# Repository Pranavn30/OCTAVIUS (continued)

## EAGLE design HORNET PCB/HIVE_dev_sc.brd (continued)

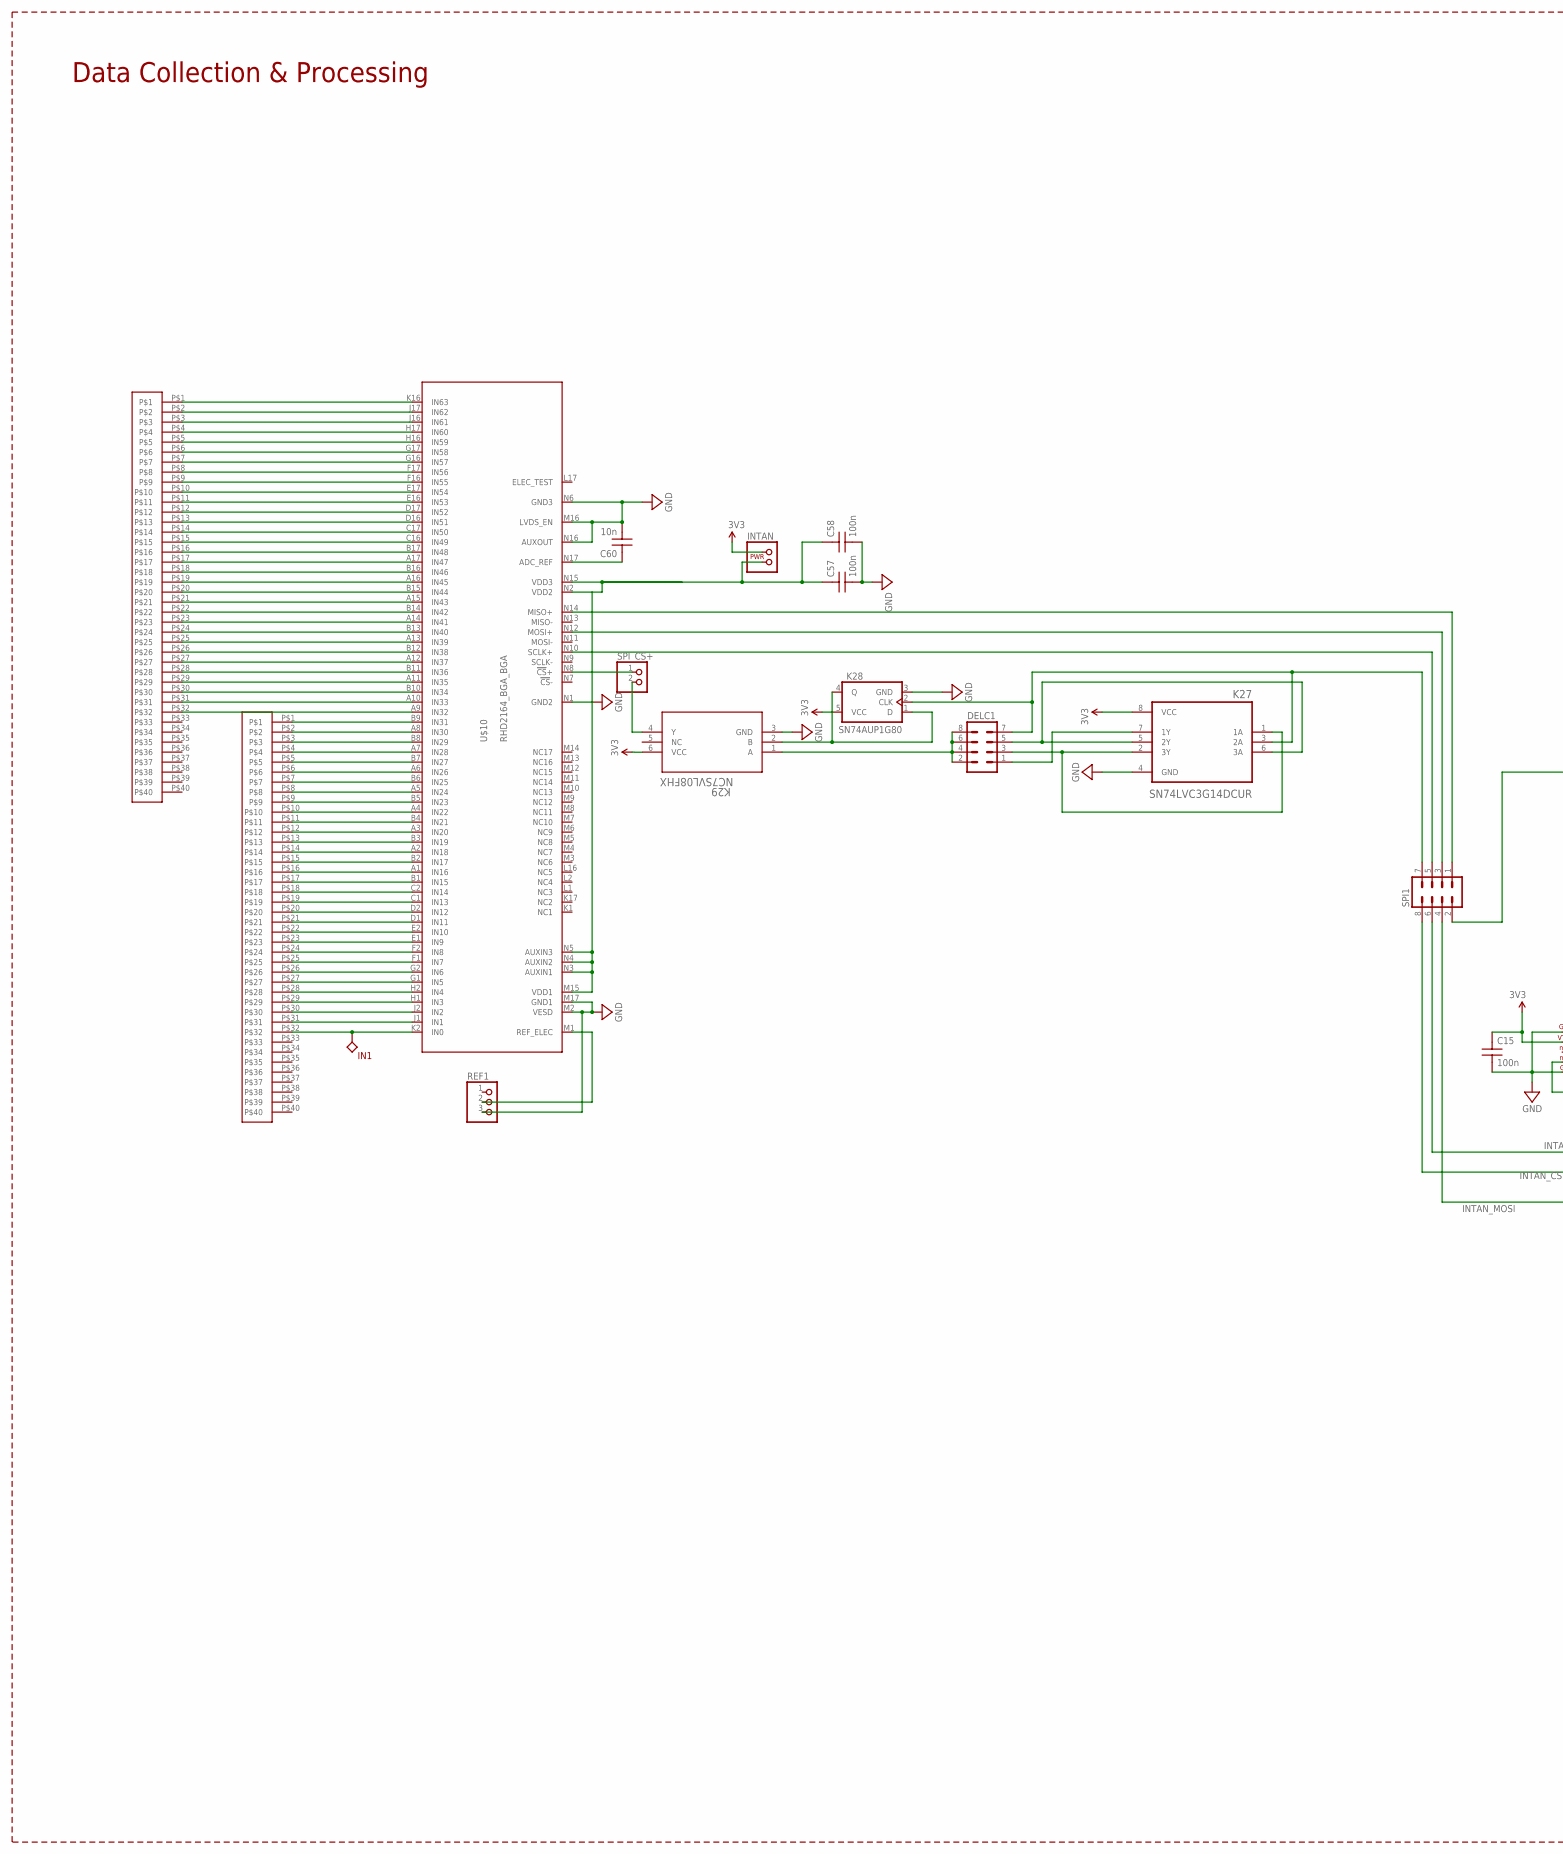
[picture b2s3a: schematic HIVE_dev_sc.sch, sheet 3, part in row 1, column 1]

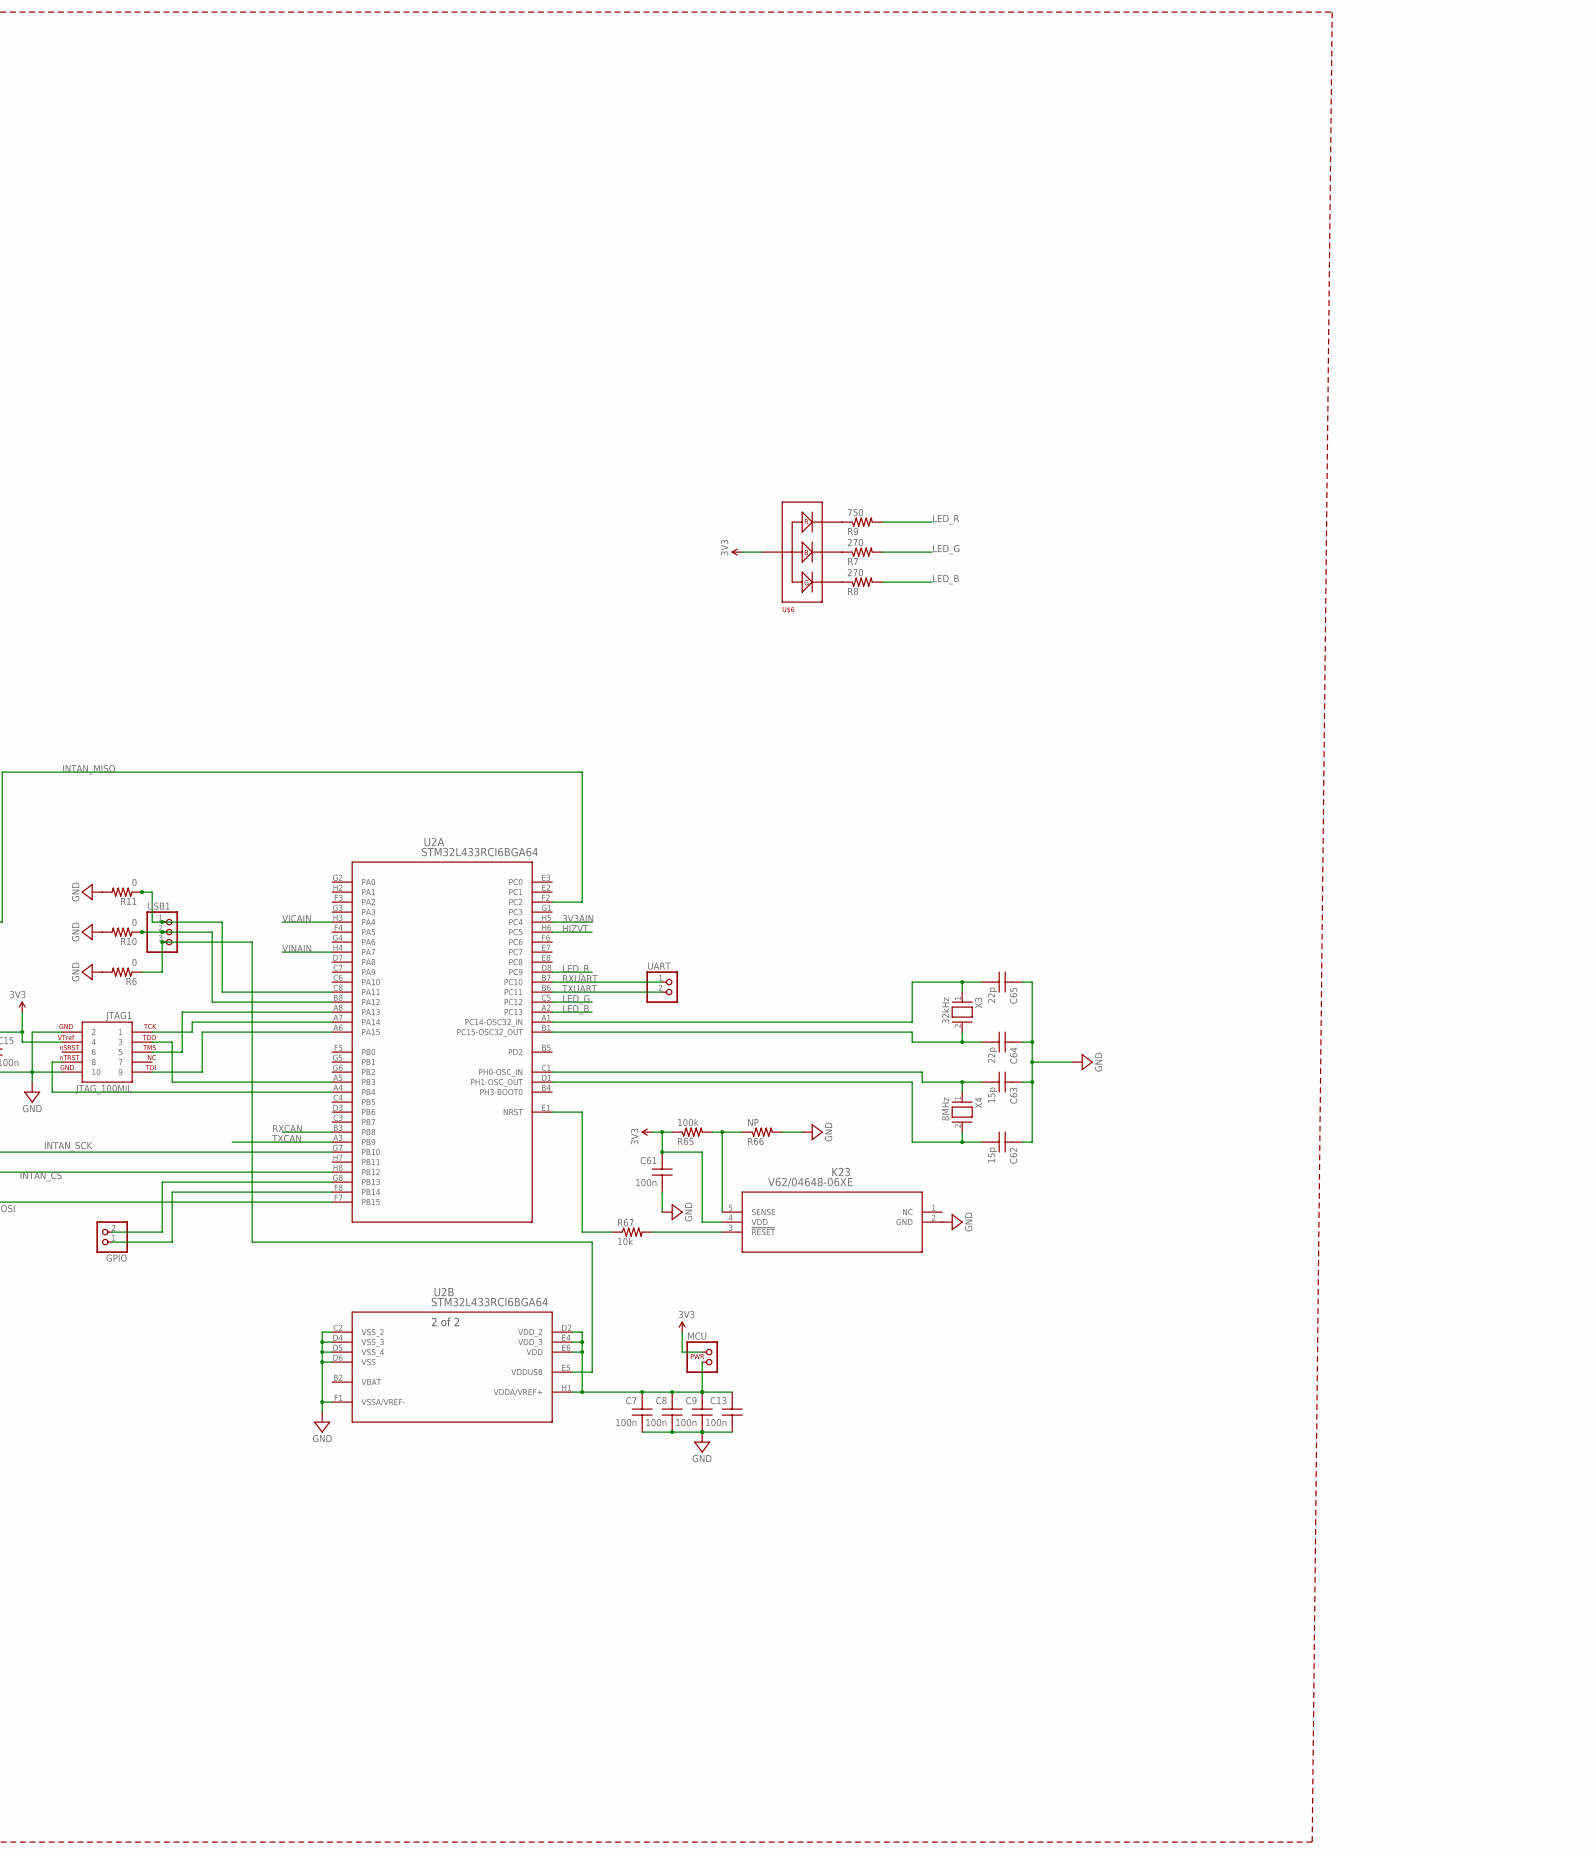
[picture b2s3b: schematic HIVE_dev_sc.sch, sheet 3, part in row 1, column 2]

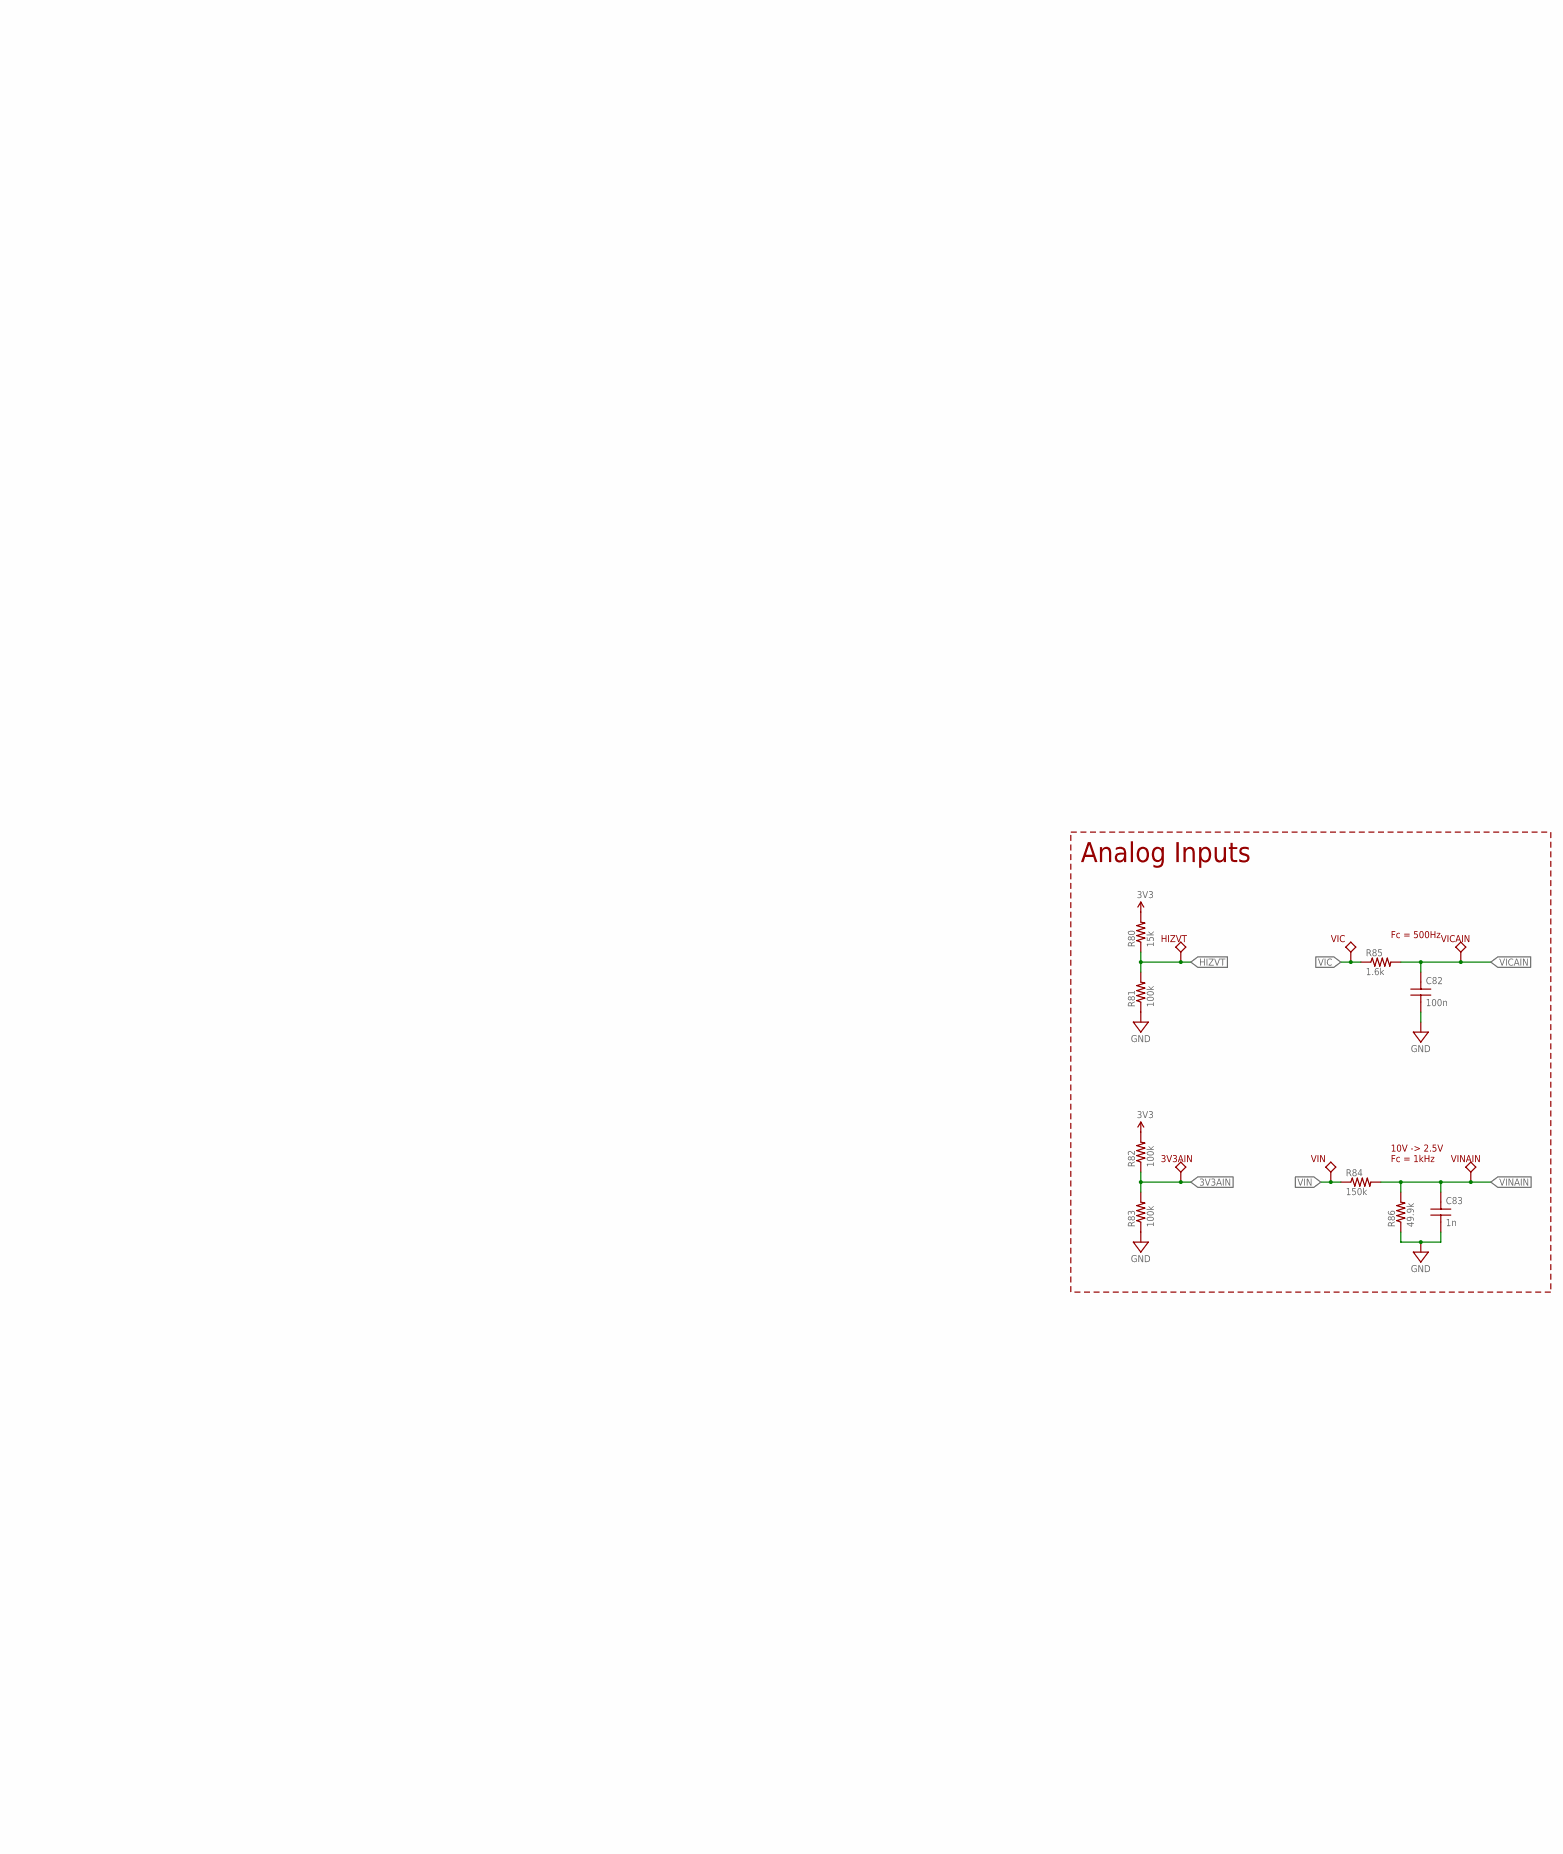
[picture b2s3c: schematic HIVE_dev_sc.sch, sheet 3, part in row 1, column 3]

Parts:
3V3AIN: TPTP5001; TP5000OR5001
C7, C8, C9, C13, C15, C57, C58, C61, C82: 100n; C0201
C60: 10n; C0201
C62, C63: 15p; C0402
C64, C65: 22p; C0402
C83: 1n; C0201
DELC1: MA04-2
GPIO: PINHD-1X2; 1X02
HIZVT: TPTP5001; TP5000OR5001
IN1: TPTP5001; TP5000OR5001
INTAN: POWERJUMP; 1X04
JTAG1: JTAG_100MIL; JTAG-10
K23: V62/04648-06XE; DCK5
K27: SN74LVC3G14DCUR; SOP50P310X90-8N
K28: SN74AUP1G80; SOT23-5
K29: NC7SVL08FHX; MICROPAK2-6_1X1_ONS
MCU: POWERJUMP; 1X04
R6, R10, R11: 0; R0201
R7, R8: 270; R0201
R9: 750; R0201
R65, R81, R82, R83: 100k; R0201
R66: NP; R0201
R67: 10k; R0201
R80: 15k; R0201
R84: 150k; R0201
R85: 1.6k; R0201
R86: 49.9k; 0201
REF1: PINHD-1X3; 1X03
SPI1: MA04-2
SPI_CS+: PINHD-1X2; 1X02
U2: STM32L433RCI6BGA64; BGA64N50P8X8_500X500X60N
U$3, U$4: 40-PIN-SAMTEC; SAMTECSFH120-01-X-D-SM-LC
U$6: WINI_KINGBRIGHT_APHF1608LSEEQBDZGKC; WINI_4-SMD
U$10: RHD2164_BGA_BGA; BGA104_9X7
UART: PINHD-1X2; 1X02
USB1: PINHD-1X3; 1X03
VIC: TPTP5001; TP5000OR5001
VICAIN: TPTP5001; TP5000OR5001
VIN: TPTP5001; TP5000OR5001
VINAIN: TPTP5001; TP5000OR5001
X3: 32kHz; ABS07
X4: 8MHz; NX5032GA

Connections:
3V3: C15.2, C61.2, INTAN.1, INTAN.2 (1), JTAG1.4, K23.4 (VDD), K27.8 (VCC), K28.5 (VCC), MCU.1, MCU.2 (1), R65.1, R80.2, R82.2, U$6.V+; also elsewhere on the board
3V3AIN: 3V3AIN.P$1, R82.1, R83.2, U2.H5 (PC4)
GND: C7.1, C8.1, C9.1, C13.1, C15.1, C57.1, C58.1, C60.1, C61.1, C62.2, C63.2, C64.2, C65.2, C82.1, C83.1, JTAG1.2, JTAG1.10, K23.2 (GND), K27.4 (GND), K28.3 (GND), K29.3 (GND), R6.2, R10.2, R11.2, R66.2, R81.1, R83.1, R86.1, REF1.3, U2.C2 (VSS_2), U2.D4 (VSS_3), U2.D5 (VSS_4), U2.D6 (VSS), U2.F1 (VSSA/VREF-), U$10.M2 (VESD), U$10.M16 (LVDS_EN), U$10.M17 (GND1), U$10.N1 (GND2), U$10.N6 (GND3), U$10.N16 (AUXOUT); also elsewhere on the board
HIZVT: HIZVT.P$1, R80.1, R81.2, U2.H6 (PC5)
INTAN_CS: SPI1.8, U2.H8 (PB12)
INTAN_MISO: SPI1.2, U2.F2 (PC2)
INTAN_MOSI: SPI1.4, U2.F7 (PB15)
INTAN_SCK: SPI1.6, U2.G7 (PB10)
LED_B: R8.2, U2.A2 (PC13)
LED_G: R7.2, U2.C5 (PC12)
LED_R: R9.2, U2.D8 (PC9)
unnamed: R67.1, U2.E1 (NRST)
unnamed: IN1.P$1, U$4.P$32, U$10.K2 (IN0)
unnamed: C60.2, U$10.N17 (ADC_REF)
unnamed: SPI_CS+.1, U$10.N8 (!CS!+)
unnamed: C57.2, C58.2, INTAN.3 (2), INTAN.4 (2), U$10.M15 (VDD1), U$10.N2 (VDD2), U$10.N3 (AUXIN1), U$10.N4 (AUXIN2), U$10.N5 (AUXIN3), U$10.N15 (VDD3)
unnamed: DELC1.7, K27.3 (2A), K28.2 (CLK), SPI1.7
unnamed: DELC1.2, DELC1.4, DELC1.6, DELC1.8, K29.1 (A)
unnamed: DELC1.5, K27.5 (2Y), K27.6 (3A)
unnamed: SPI1.5, U$10.N10 (SCLK+)
unnamed: DELC1.3, K27.1 (1A), K27.2 (3Y)
unnamed: DELC1.1, K27.7 (1Y)
unnamed: SPI1.1, U$10.N14 (MISO+)
unnamed: SPI1.3, U$10.N12 (MOSI+)
unnamed: K23.3 (!RESET), R67.2
unnamed: U$4.P$31, U$10.J1 (IN1)
unnamed: U$4.P$30, U$10.J2 (IN2)
unnamed: U$4.P$29, U$10.H1 (IN3)
unnamed: U$4.P$28, U$10.H2 (IN4)
unnamed: U$4.P$27, U$10.G1 (IN5)
unnamed: U$4.P$26, U$10.G2 (IN6)
unnamed: U$4.P$25, U$10.F1 (IN7)
unnamed: U$4.P$24, U$10.F2 (IN8)
unnamed: U$4.P$23, U$10.E1 (IN9)
unnamed: U$4.P$22, U$10.E2 (IN10)
unnamed: U$4.P$21, U$10.D1 (IN11)
unnamed: U$4.P$20, U$10.D2 (IN12)
unnamed: U$4.P$19, U$10.C1 (IN13)
unnamed: U$4.P$18, U$10.C2 (IN14)
unnamed: U$4.P$17, U$10.B1 (IN15)
unnamed: U$4.P$16, U$10.A1 (IN16)
unnamed: U$4.P$15, U$10.B2 (IN17)
unnamed: U$4.P$14, U$10.A2 (IN18)
unnamed: U$4.P$13, U$10.B3 (IN19)
unnamed: U$4.P$12, U$10.A3 (IN20)
unnamed: U$4.P$11, U$10.B4 (IN21)
unnamed: U$4.P$10, U$10.A4 (IN22)
unnamed: U$4.P$9, U$10.B5 (IN23)
unnamed: U$4.P$8, U$10.A5 (IN24)
unnamed: U$4.P$7, U$10.B6 (IN25)
unnamed: U$4.P$6, U$10.A6 (IN26)
unnamed: U$4.P$5, U$10.B7 (IN27)
unnamed: U$4.P$4, U$10.A7 (IN28)
unnamed: U$4.P$3, U$10.B8 (IN29)
unnamed: U$4.P$2, U$10.A8 (IN30)
unnamed: U$4.P$1, U$10.B9 (IN31)
unnamed: U$3.P$32, U$10.A9 (IN32)
unnamed: U$3.P$31, U$10.A10 (IN33)
unnamed: U$3.P$30, U$10.B10 (IN34)
unnamed: U$3.P$29, U$10.A11 (IN35)
unnamed: U$3.P$28, U$10.B11 (IN36)
unnamed: U$3.P$27, U$10.A12 (IN37)
unnamed: U$3.P$26, U$10.B12 (IN38)
unnamed: U$3.P$25, U$10.A13 (IN39)
unnamed: U$3.P$24, U$10.B13 (IN40)
unnamed: U$3.P$23, U$10.A14 (IN41)
unnamed: U$3.P$22, U$10.B14 (IN42)
unnamed: U$3.P$21, U$10.A15 (IN43)
unnamed: U$3.P$20, U$10.B15 (IN44)
unnamed: U$3.P$19, U$10.A16 (IN45)
unnamed: U$3.P$18, U$10.B16 (IN46)
unnamed: U$3.P$17, U$10.A17 (IN47)
unnamed: U$3.P$16, U$10.B17 (IN48)
unnamed: U$3.P$15, U$10.C16 (IN49)
unnamed: U$3.P$14, U$10.C17 (IN50)
unnamed: U$3.P$13, U$10.D16 (IN51)
unnamed: U$3.P$12, U$10.D17 (IN52)
unnamed: U$3.P$11, U$10.E16 (IN53)
unnamed: U$3.P$10, U$10.E17 (IN54)
unnamed: U$3.P$9, U$10.F16 (IN55)
unnamed: U$3.P$8, U$10.F17 (IN56)
unnamed: U$3.P$7, U$10.G16 (IN57)
unnamed: U$3.P$6, U$10.G17 (IN58)
unnamed: U$3.P$5, U$10.H16 (IN59)
unnamed: U$3.P$4, U$10.H17 (IN60)
unnamed: U$3.P$3, U$10.J16 (IN61)
unnamed: U$3.P$2, U$10.J17 (IN62)
unnamed: U$3.P$1, U$10.K16 (IN63)
unnamed: JTAG1.3, U2.A5 (PB3)
unnamed: JTAG1.9, U2.A6 (PA15)
unnamed: JTAG1.1, U2.A7 (PA14)
unnamed: JTAG1.8, U2.A4 (PB4)
unnamed: JTAG1.5, U2.A8 (PA13)
unnamed: REF1.2, U$10.M1 (REF_ELEC)
unnamed: R7.1, U$6.B
unnamed: R10.1, U2.B8 (PA12), USB1.2
unnamed: R6.1, U2.E5 (VDDUSB), USB1.3
unnamed: R11.1, U2.C8 (PA11), USB1.1
unnamed: R8.1, U$6.G
unnamed: R9.1, U$6.R
unnamed: GPIO.2, U2.G8 (PB13)
unnamed: GPIO.1, U2.F8 (PB14)
unnamed: K29.4 (Y), SPI_CS+.2
unnamed: C65.1, U2.A1 (PC14-OSC32_IN), X3.1
unnamed: C7.2, C8.2, C9.2, C13.2, MCU.3 (2), MCU.4 (2), U2.D2 (VDD_2), U2.E4 (VDD_3), U2.E6 (VDD), U2.H1 (VDDA/VREF+)
unnamed: K23.5 (SENSE), R65.2, R66.1
unnamed: C63.1, U2.C1 (PH0-OSC_IN), X4.1
unnamed: C64.1, U2.B1 (PC15-OSC32_OUT), X3.2
unnamed: C62.1, U2.D1 (PH1-OSC_OUT), X4.2
unnamed: K28.1 (D), K28.4 (Q), K29.2 (B)
RXCAN: U2.B3 (PB8); also elsewhere on the board
RXUART: U2.B7 (PC10), UART.1
TXCAN: U2.A3 (PB9); also elsewhere on the board
TXUART: U2.B6 (PC11), UART.2
VBAT: U2.B2 (VBAT)
VCC: K29.6 (VCC)
VIC: R85.1, VIC.P$1; also elsewhere on the board
VICAIN: C82.2, R85.2, U2.H3 (PA4), VICAIN.P$1
VIN: R84.1, VIN.P$1; also elsewhere on the board
VINAIN: C83.2, R84.2, R86.2, U2.H4 (PA7), VINAIN.P$1

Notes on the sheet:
Data Collection & Processing
Analog Inputs
Fc = 500Hz
10V -> 2.5V Fc = 1kHz

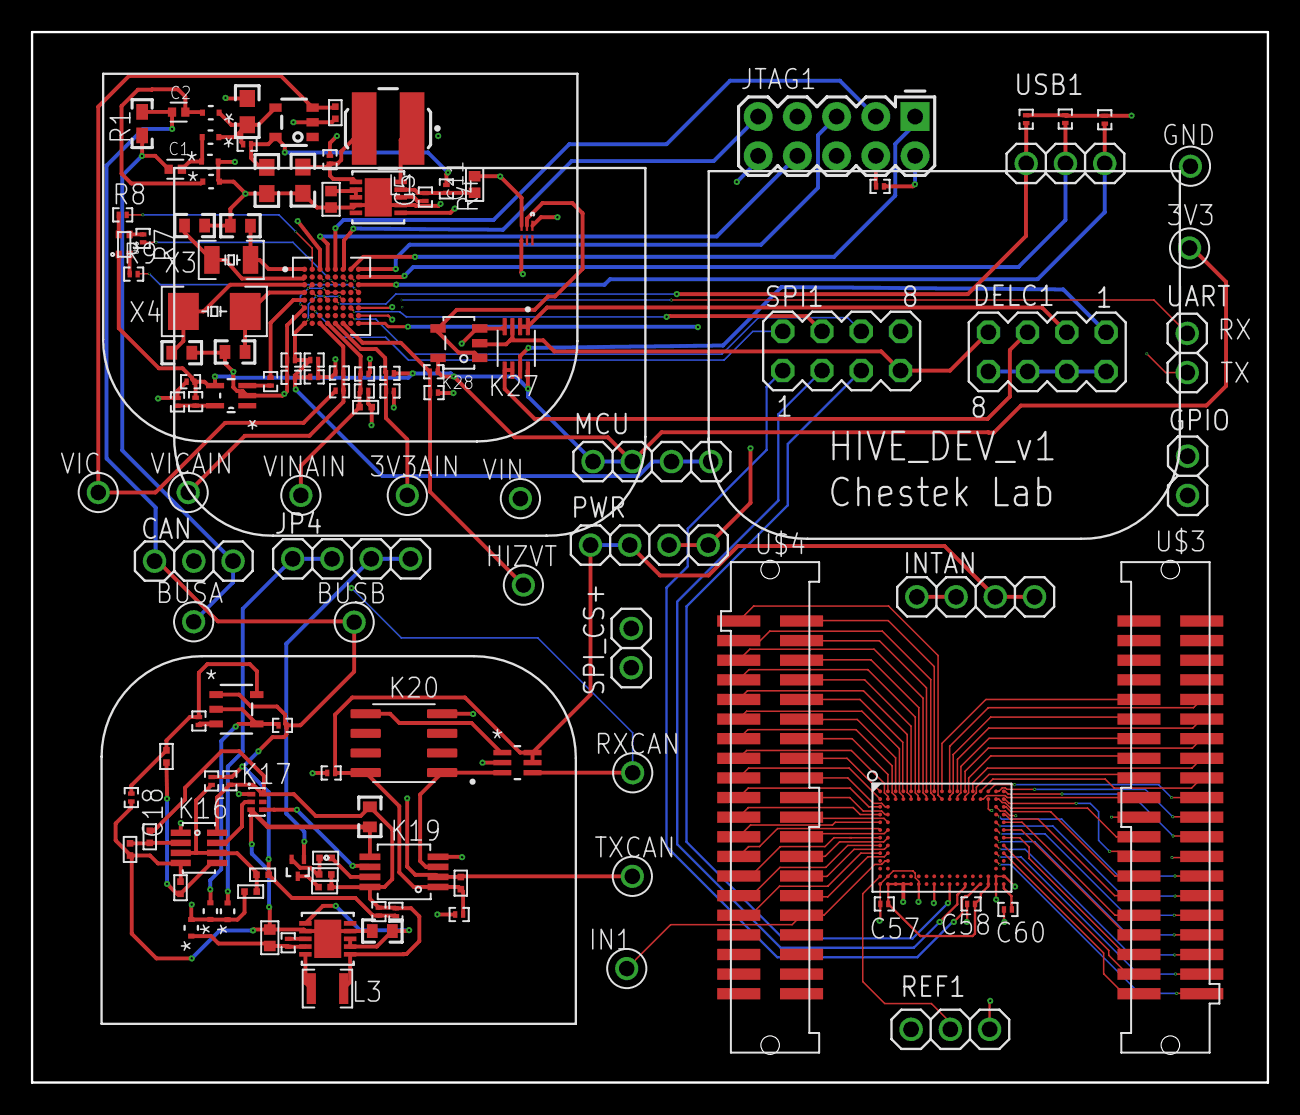
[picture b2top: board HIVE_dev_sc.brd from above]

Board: 4 copper layers, 80.0 x 68.0 mm, 123 parts (0 on the bottom side), 151 nets.
